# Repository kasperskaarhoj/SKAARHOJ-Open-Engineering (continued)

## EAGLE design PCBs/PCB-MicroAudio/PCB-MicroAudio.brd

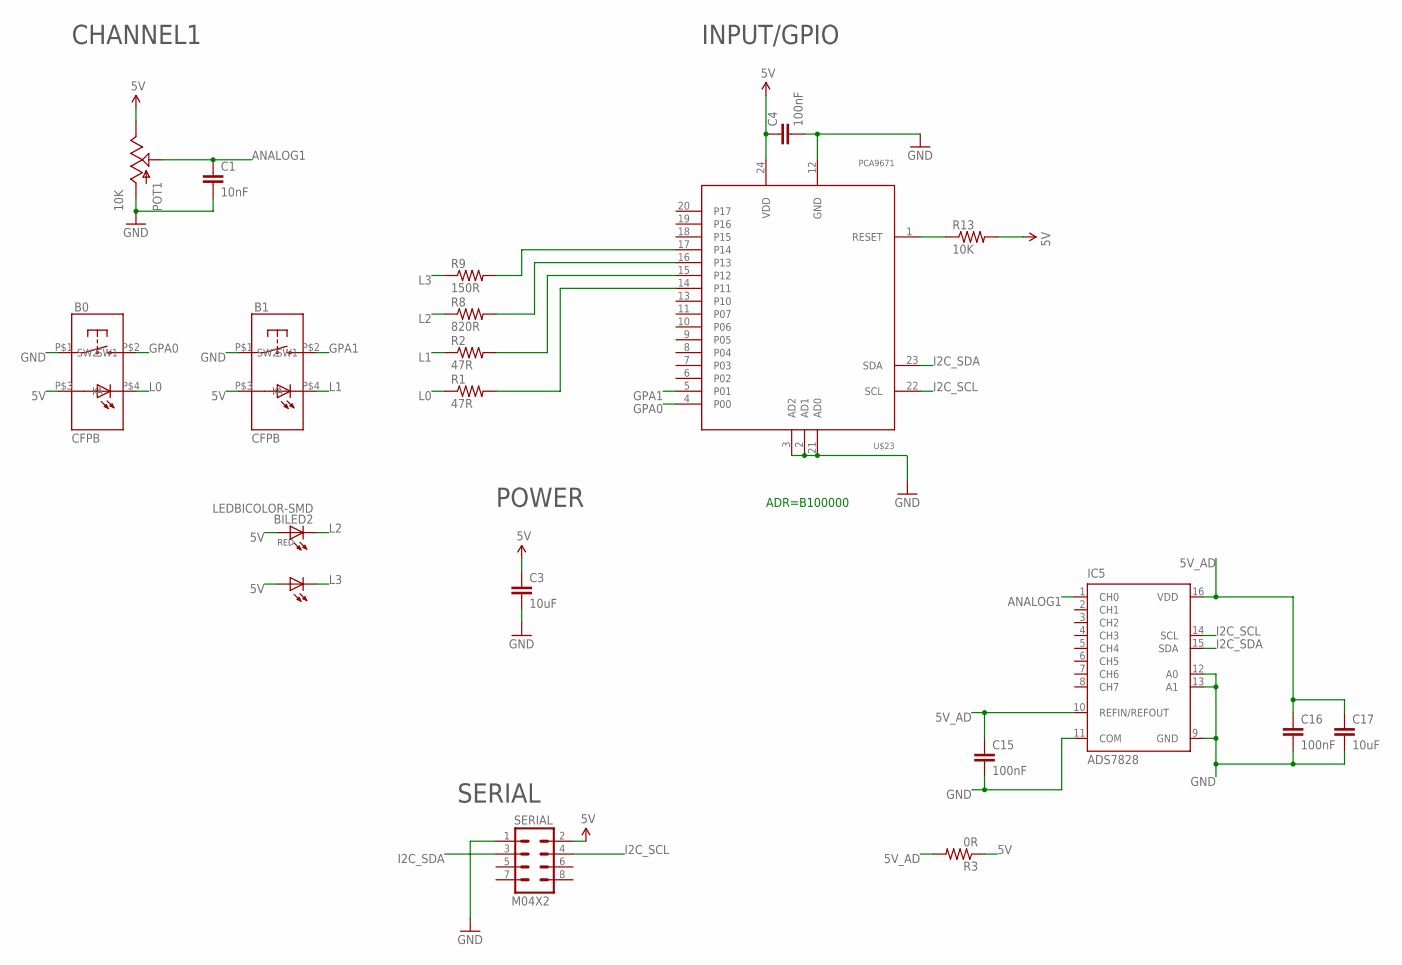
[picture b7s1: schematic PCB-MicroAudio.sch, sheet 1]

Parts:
B0, B1: CFPB; CFPB-6/9MM
BILED2: LEDBICOLOR-SMD
C1: 10nF; 0603-CAP
C3, C17: 10uF; 0805
C4, C15, C16: 100nF; 0603-CAP
IC5: ADS7828; TSSOP16-PW
POT1: 10K; ALPS_POT
R1, R2: 47R; 0603-RES
R3: 0R; 0603-RES
R8: 820R; 0603-RES
R9: 150R; 0603-RES
R13: 10K; 0603-RES
SERIAL: M04X2; 2X4
U$23: PCA9671; TSSOP24

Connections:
5V: B0.P$3 (A), B1.P$3 (A), BILED2.P$1 (A), BILED2.P$3 (A1), C3.1, C4.1, POT1.P$1 (E), R3.1, R13.2, SERIAL.2, U$23.24 (VDD)
5V_AD: C15.1, C16.1, C17.1, IC5.10 (REFIN/REFOUT), IC5.16 (VDD), R3.2
ANALOG1: C1.1, IC5.1 (CH0), POT1.P$2 (S)
GND: B0.P$1 (SW1), B1.P$1 (SW1), C1.2, C3.2, C4.2, C15.2, C16.2, C17.2, IC5.9 (GND), IC5.11 (COM), IC5.12 (A0), IC5.13 (A1), POT1.P$3 (A), SERIAL.1, U$23.2 (AD1), U$23.3 (AD2), U$23.12 (GND), U$23.21 (AD0)
GPA0: B0.P$2 (SW2), U$23.4 (P00)
GPA1: B1.P$2 (SW2), U$23.5 (P01)
I2C_SCL: IC5.14 (SCL), SERIAL.4, U$23.22 (SCL)
I2C_SDA: IC5.15 (SDA), SERIAL.3, U$23.23 (SDA)
L0: B0.P$4 (K), R1.1
L1: B1.P$4 (K), R2.1
L2: BILED2.P$2 (C), R8.1
L3: BILED2.P$4 (C1), R9.1
unnamed: R9.2, U$23.17 (P14)
unnamed: R8.2, U$23.16 (P13)
unnamed: R2.2, U$23.15 (P12)
unnamed: R1.2, U$23.14 (P11)
unnamed: R13.1, U$23.1 (RESET)

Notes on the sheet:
SERIAL
POWER
CHANNEL1
INPUT/GPIO
ADR=B100000

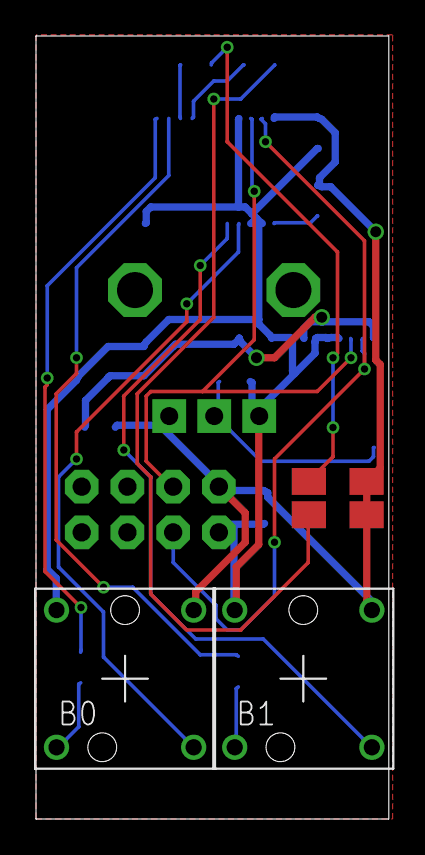
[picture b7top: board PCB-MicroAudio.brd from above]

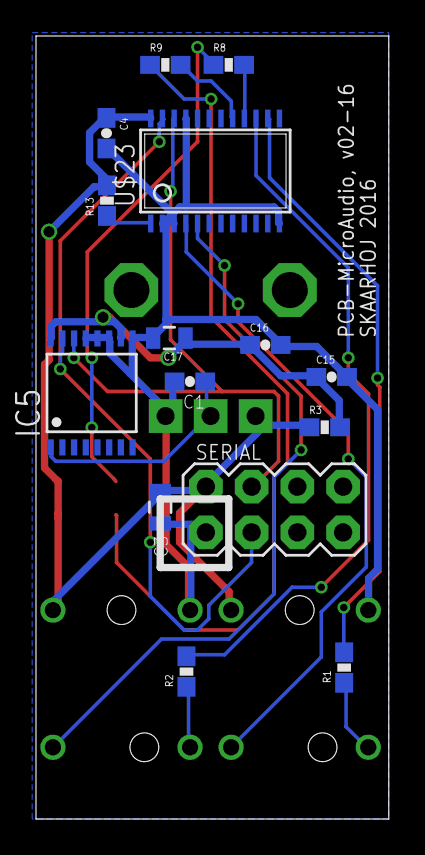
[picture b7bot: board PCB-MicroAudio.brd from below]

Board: 2 copper layers, 19.6 x 43.5 mm, 19 parts (15 on the bottom side), 17 nets.

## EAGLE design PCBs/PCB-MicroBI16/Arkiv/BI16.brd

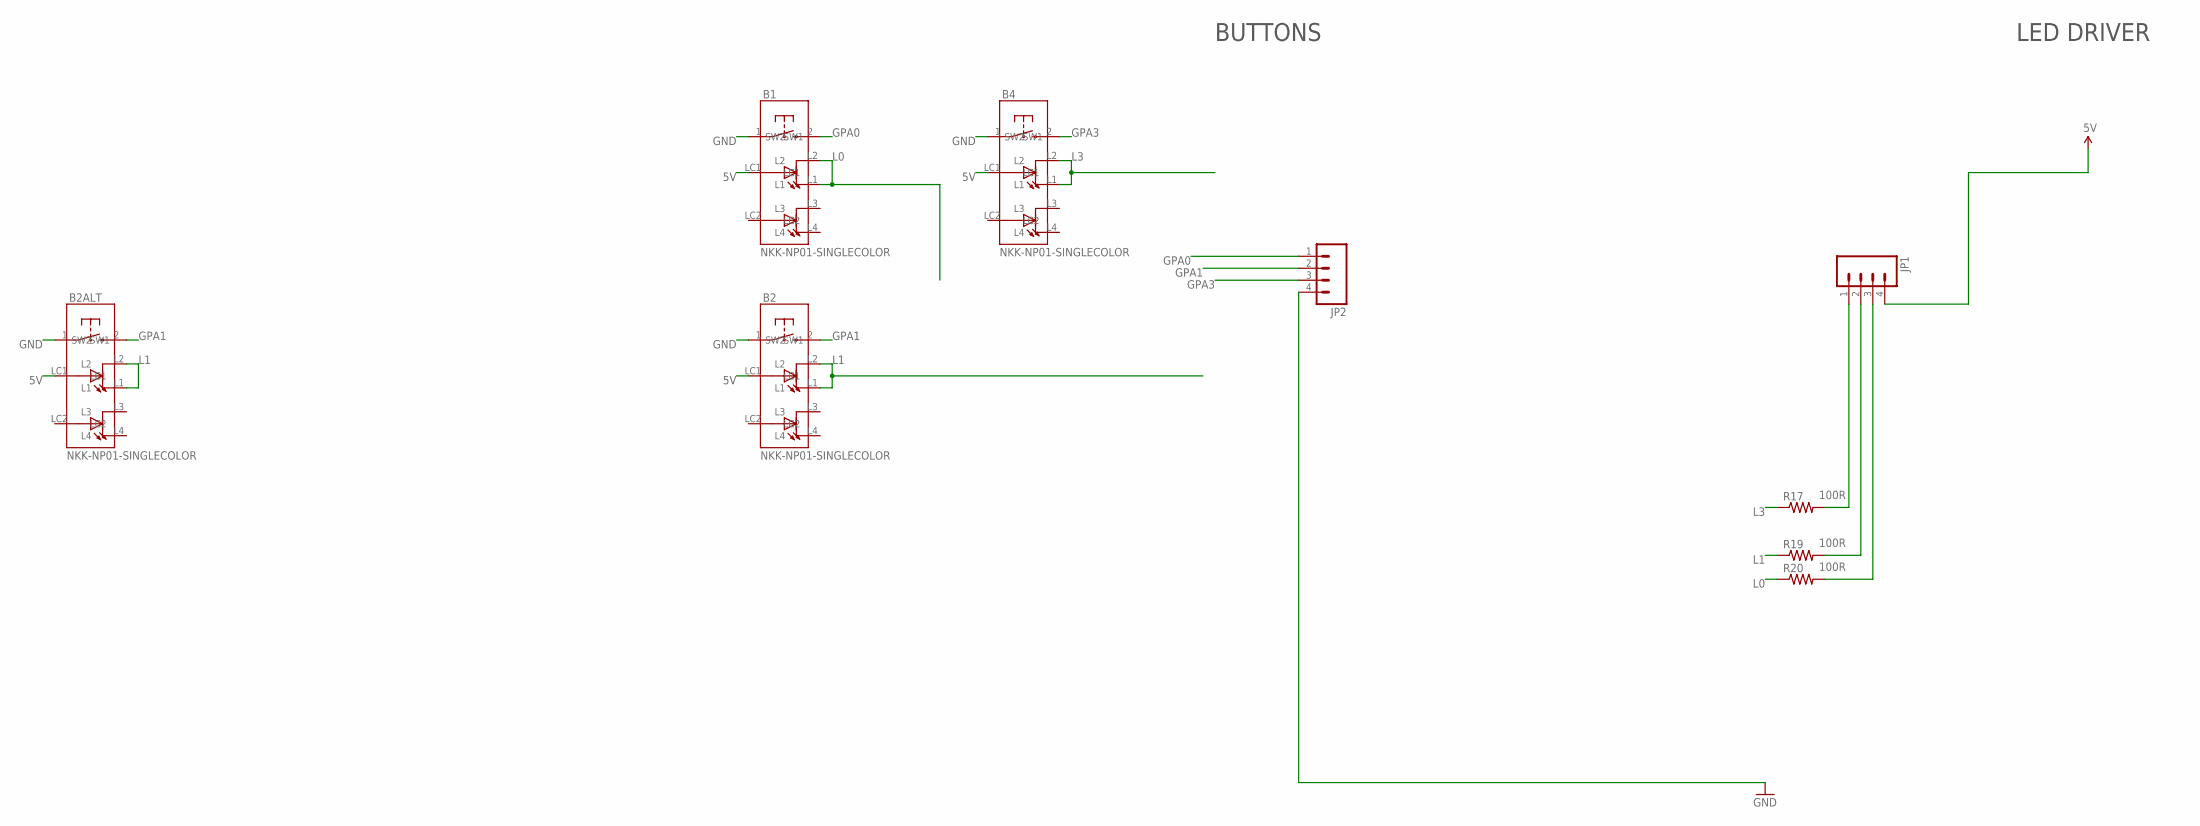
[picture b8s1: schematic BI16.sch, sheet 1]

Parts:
B1, B2, B2ALT, B4: NKK-NP01-SINGLECOLOR; NKK-NP01
JP1, JP2: M04LOCK; 1X04_LOCK
R17, R19, R20: 100R; 0603-RES

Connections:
5V: B1.LC1, B2.LC1, B2ALT.LC1, B4.LC1, JP1.4
GND: B1.1 (SW1), B2.1 (SW1), B2ALT.1 (SW1), B4.1 (SW1), JP2.4
GPA0: B1.2 (SW2), JP2.1
GPA1: B2.2 (SW2), B2ALT.2 (SW2), JP2.2
GPA3: B4.2 (SW2), JP2.3
L0: B1.L1, B1.L2, R20.1
L1: B2.L1, B2.L2, B2ALT.L1, B2ALT.L2, R19.1
L3: B4.L1, B4.L2, R17.1
unnamed: JP1.1, R17.2
unnamed: JP1.2, R19.2
unnamed: JP1.3, R20.2

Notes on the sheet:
BUTTONS
LED DRIVER

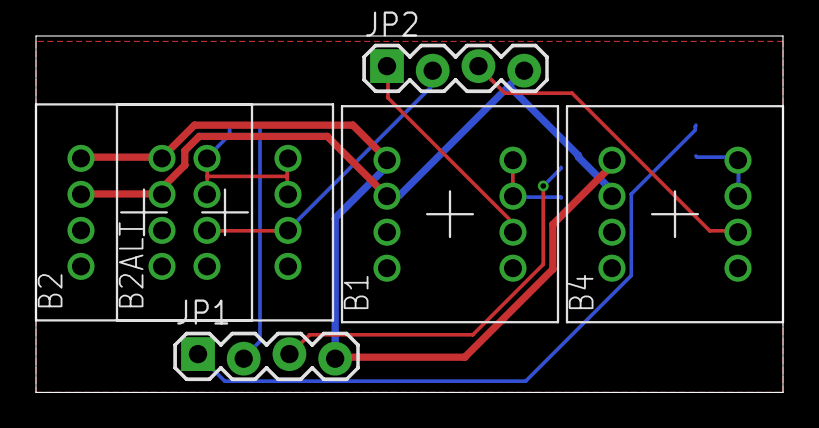
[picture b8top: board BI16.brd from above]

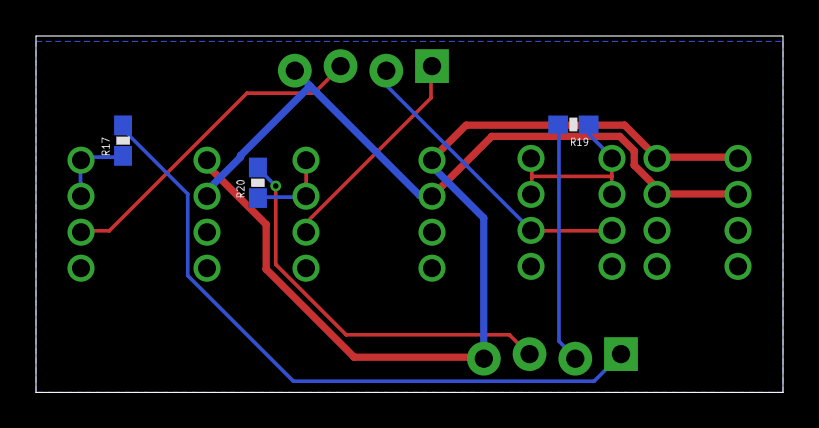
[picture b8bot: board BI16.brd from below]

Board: 2 copper layers, 41.5 x 19.8 mm, 9 parts (3 on the bottom side), 11 nets.
